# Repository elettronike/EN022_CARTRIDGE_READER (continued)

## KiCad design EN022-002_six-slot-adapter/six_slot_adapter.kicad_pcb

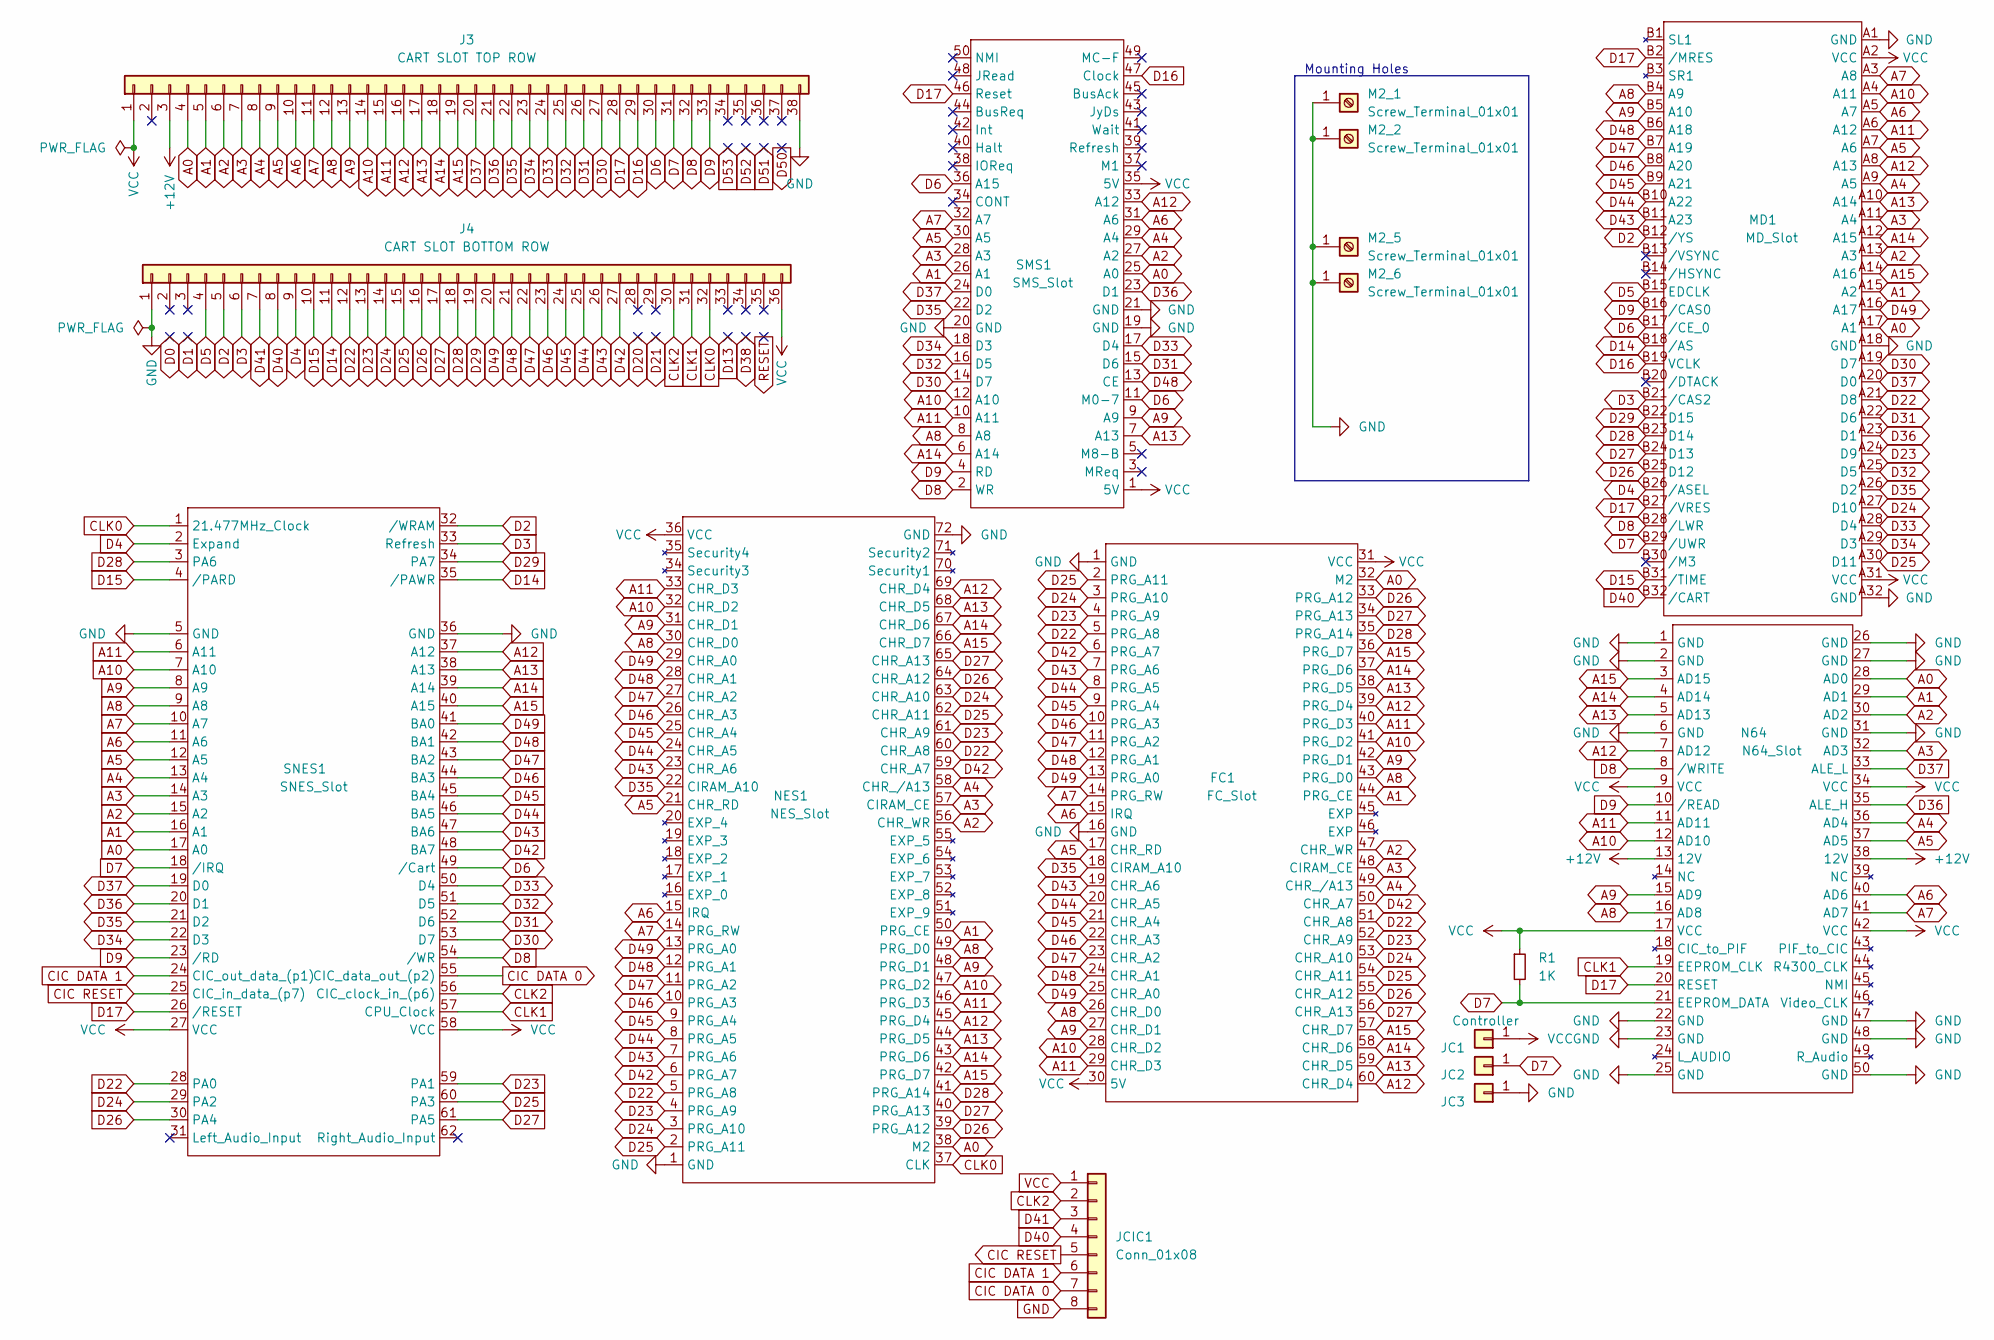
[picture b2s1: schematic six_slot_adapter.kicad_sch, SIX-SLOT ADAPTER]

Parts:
FC1: FC_Slot
J3: CART SLOT TOP ROW; PinSocket_1x38_P2.54mm_Vertical
J4: CART SLOT BOTTOM ROW; PinSocket_1x36_P2.54mm_Vertical
JC1: Controller; PinHeader_1x01_P2.54mm_Vertical
JC2, JC3: Conn_01x01; PinHeader_1x01_P2.54mm_Vertical
JCIC1: Conn_01x08; PinHeader_1x08_P2.54mm_Vertical
M2_1, M2_2, M2_5, M2_6: Screw_Terminal_01x01; MountingHole_2.2mm_M2_ISO7380_Pad
MD1: MD_Slot
N64: N64_Slot; N64 Slot
NES1: NES_Slot
R1: 1K; R_Axial_DIN0207_L6.3mm_D2.5mm_P10.16mm_Horizontal
SMS1: SMS_Slot
SNES1: SNES_Slot; SNES Slot

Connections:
+12V: J3.3, N64.13 (12V), N64.38 (12V)
A0: FC1.32 (M2), J3.4, MD1.A17 (A1), N64.28 (AD0), NES1.38 (M2), SMS1.25 (A0), SNES1.17 (A0)
A1: FC1.44 (PRG_CE), J3.5, MD1.A15 (A2), N64.29 (AD1), NES1.50 (PRG_CE), SMS1.26 (A1), SNES1.16 (A1)
A2: FC1.47 (CHR_WR), J3.6, MD1.A13 (A3), N64.30 (AD2), NES1.56 (CHR_WR), SMS1.27 (A2), SNES1.15 (A2)
A3: FC1.48 (CIRAM_CE), J3.7, MD1.A11 (A4), N64.32 (AD3), NES1.57 (CIRAM_CE), SMS1.28 (A3), SNES1.14 (A3)
A4: FC1.49 (CHR_/A13), J3.8, MD1.A9 (A5), N64.36 (AD4), NES1.58 (CHR_/A13), SMS1.29 (A4), SNES1.13 (A4)
A5: FC1.17 (CHR_RD), J3.9, MD1.A7 (A6), N64.37 (AD5), NES1.21 (CHR_RD), SMS1.30 (A5), SNES1.12 (A5)
A6: FC1.15 (IRQ), J3.10, MD1.A5 (A7), N64.40 (AD6), NES1.15 (IRQ), SMS1.31 (A6), SNES1.11 (A6)
A7: FC1.14 (PRG_RW), J3.11, MD1.A3 (A8), N64.41 (AD7), NES1.14 (PRG_RW), SMS1.32 (A7), SNES1.10 (A7)
A8: FC1.26 (CHR_D0), FC1.43 (PRG_D0), J3.12, MD1.B4 (A9), N64.16 (AD8), NES1.30 (CHR_D0), NES1.49 (PRG_D0), SMS1.8 (A8), SNES1.9 (A8)
A9: FC1.27 (CHR_D1), FC1.42 (PRG_D1), J3.13, MD1.B5 (A10), N64.15 (AD9), NES1.31 (CHR_D1), NES1.48 (PRG_D1), SMS1.9 (A9), SNES1.8 (A9)
A10: FC1.28 (CHR_D2), FC1.41 (PRG_D2), J3.14, MD1.A4 (A11), N64.12 (AD10), NES1.32 (CHR_D2), NES1.47 (PRG_D2), SMS1.12 (A10), SNES1.7 (A10)
A11: FC1.29 (CHR_D3), FC1.40 (PRG_D3), J3.15, MD1.A6 (A12), N64.11 (AD11), NES1.33 (CHR_D3), NES1.46 (PRG_D3), SMS1.10 (A11), SNES1.6 (A11)
A12: FC1.39 (PRG_D4), FC1.60 (CHR_D4), J3.16, MD1.A8 (A13), N64.7 (AD12), NES1.45 (PRG_D4), NES1.69 (CHR_D4), SMS1.33 (A12), SNES1.37 (A12)
A13: FC1.38 (PRG_D5), FC1.59 (CHR_D5), J3.17, MD1.A10 (A14), N64.5 (AD13), NES1.44 (PRG_D5), NES1.68 (CHR_D5), SMS1.7 (A13), SNES1.38 (A13)
A14: FC1.37 (PRG_D6), FC1.58 (CHR_D6), J3.18, MD1.A12 (A15), N64.4 (AD14), NES1.43 (PRG_D6), NES1.67 (CHR_D6), SMS1.6 (A14), SNES1.39 (A14)
A15: FC1.36 (PRG_D7), FC1.57 (CHR_D7), J3.19, MD1.A14 (A16), N64.3 (AD15), NES1.42 (PRG_D7), NES1.66 (CHR_D7), SNES1.40 (A15)
CIC DATA 0: JCIC1.7, SNES1.55 (CIC_data_out_(p2))
CIC DATA 1: JCIC1.6, SNES1.24 (CIC_out_data_(p1))
CIC RESET: JCIC1.5, SNES1.25 (CIC_in_data_(p7))
CLK0: J4.32, NES1.37 (CLK), SNES1.1 (21.477MHz_Clock)
CLK1: J4.31, N64.19 (EEPROM_CLK), SNES1.57 (CPU_Clock)
CLK2: J4.30, JCIC1.2, SNES1.56 (CIC_clock_in_(p6))
D2: J4.5, MD1.B12 (/YS), SNES1.32 (/WRAM)
D3: J4.6, MD1.B21 (/CAS2), SNES1.33 (Refresh)
D4: J4.9, MD1.B26 (/ASEL), SNES1.2 (Expand)
D5: J4.4, MD1.B15 (EDCLK)
D6: J3.30, MD1.B17 (/CE_0), SMS1.11 (M0-7), SMS1.36 (A15), SNES1.49 (/Cart)
D7: J3.31, JC2.1, MD1.B29 (/UWR), N64.21 (EEPROM_DATA), R1.2, SNES1.18 (/IRQ)
D8: J3.32, MD1.B28 (/LWR), N64.8 (/WRITE), SMS1.2 (WR), SNES1.54 (/WR)
D9: J3.33, MD1.B16 (/CAS0), N64.10 (/READ), SMS1.4 (RD), SNES1.23 (/RD)
D14: J4.11, MD1.B18 (/AS), SNES1.35 (/PAWR)
D15: J4.10, MD1.B31 (/TIME), SNES1.4 (/PARD)
D16: J3.29, MD1.B19 (VCLK), SMS1.47 (Clock)
D17: J3.28, MD1.B2 (/MRES), MD1.B27 (/VRES), N64.20 (RESET), SMS1.46 (Reset), SNES1.26 (/RESET)
D22: FC1.5 (PRG_A8), FC1.51 (CHR_A8), J4.12, MD1.A21 (D8), NES1.5 (PRG_A8), NES1.60 (CHR_A8), SNES1.28 (PA0)
D23: FC1.4 (PRG_A9), FC1.52 (CHR_A9), J4.13, MD1.A24 (D9), NES1.4 (PRG_A9), NES1.61 (CHR_A9), SNES1.59 (PA1)
D24: FC1.3 (PRG_A10), FC1.53 (CHR_A10), J4.14, MD1.A27 (D10), NES1.3 (PRG_A10), NES1.63 (CHR_A10), SNES1.29 (PA2)
D25: FC1.2 (PRG_A11), FC1.54 (CHR_A11), J4.15, MD1.A30 (D11), NES1.2 (PRG_A11), NES1.62 (CHR_A11), SNES1.60 (PA3)
D26: FC1.33 (PRG_A12), FC1.55 (CHR_A12), J4.16, MD1.B25 (D12), NES1.39 (PRG_A12), NES1.64 (CHR_A12), SNES1.30 (PA4)
D27: FC1.34 (PRG_A13), FC1.56 (CHR_A13), J4.17, MD1.B24 (D13), NES1.40 (PRG_A13), NES1.65 (CHR_A13), SNES1.61 (PA5)
D28: FC1.35 (PRG_A14), J4.18, MD1.B23 (D14), NES1.41 (PRG_A14), SNES1.3 (PA6)
D29: J4.19, MD1.B22 (D15), SNES1.34 (PA7)
D30: J3.27, MD1.A19 (D7), SMS1.14 (D7), SNES1.53 (D7)
D31: J3.26, MD1.A22 (D6), SMS1.15 (D6), SNES1.52 (D6)
D32: J3.25, MD1.A25 (D5), SMS1.16 (D5), SNES1.51 (D5)
D33: J3.24, MD1.A28 (D4), SMS1.17 (D4), SNES1.50 (D4)
D34: J3.23, MD1.A29 (D3), SMS1.18 (D3), SNES1.22 (D3)
D35: FC1.18 (CIRAM_A10), J3.22, MD1.A26 (D2), NES1.22 (CIRAM_A10), SMS1.22 (D2), SNES1.21 (D2)
D36: J3.21, MD1.A23 (D1), N64.35 (ALE_H), SMS1.23 (D1), SNES1.20 (D1)
D37: J3.20, MD1.A20 (D0), N64.33 (ALE_L), SMS1.24 (D0), SNES1.19 (D0)
D40: J4.8, JCIC1.4, MD1.B32 (/CART)
D41: J4.7, JCIC1.3
D42: FC1.6 (PRG_A7), FC1.50 (CHR_A7), J4.27, NES1.6 (PRG_A7), NES1.59 (CHR_A7), SNES1.48 (BA7)
D43: FC1.7 (PRG_A6), FC1.19 (CHR_A6), J4.26, MD1.B11 (A23), NES1.7 (PRG_A6), NES1.23 (CHR_A6), SNES1.47 (BA6)
D44: FC1.8 (PRG_A5), FC1.20 (CHR_A5), J4.25, MD1.B10 (A22), NES1.8 (PRG_A5), NES1.24 (CHR_A5), SNES1.46 (BA5)
D45: FC1.9 (PRG_A4), FC1.21 (CHR_A4), J4.24, MD1.B9 (A21), NES1.9 (PRG_A4), NES1.25 (CHR_A4), SNES1.45 (BA4)
D46: FC1.10 (PRG_A3), FC1.22 (CHR_A3), J4.23, MD1.B8 (A20), NES1.10 (PRG_A3), NES1.26 (CHR_A3), SNES1.44 (BA3)
D47: FC1.11 (PRG_A2), FC1.23 (CHR_A2), J4.22, MD1.B7 (A19), NES1.11 (PRG_A2), NES1.27 (CHR_A2), SNES1.43 (BA2)
D48: FC1.12 (PRG_A1), FC1.24 (CHR_A1), J4.21, MD1.B6 (A18), NES1.12 (PRG_A1), NES1.28 (CHR_A1), SMS1.13 (CE), SNES1.42 (BA1)
D49: FC1.13 (PRG_A0), FC1.25 (CHR_A0), J4.20, MD1.A16 (A17), NES1.13 (PRG_A0), NES1.29 (CHR_A0), SNES1.41 (BA0)
GND: FC1.1 (GND), FC1.16 (GND), J3.38, J4.1, JC3.1, JCIC1.8, M2_1.1, M2_2.1, M2_5.1, M2_6.1, MD1.A1 (GND), MD1.A18 (GND), MD1.A32 (GND), N64.1 (GND), N64.2 (GND), N64.6 (GND), N64.22 (GND), N64.23 (GND), N64.25 (GND), N64.26 (GND), N64.27 (GND), N64.31 (GND), N64.47 (GND), N64.48 (GND), N64.50 (GND), NES1.1 (GND), NES1.72 (GND), SMS1.19 (GND), SMS1.20 (GND), SMS1.21 (GND), SNES1.5 (GND), SNES1.36 (GND)
VCC: FC1.30 (5V), FC1.31 (VCC), J3.1, J4.36, JC1.1, JCIC1.1, MD1.A2 (VCC), MD1.A31 (VCC), N64.9 (VCC), N64.17 (VCC), N64.34 (VCC), N64.42 (VCC), NES1.36 (VCC), R1.1, SMS1.1 (5V), SMS1.35 (5V), SNES1.27 (VCC), SNES1.58 (VCC)

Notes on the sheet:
Mounting Holes

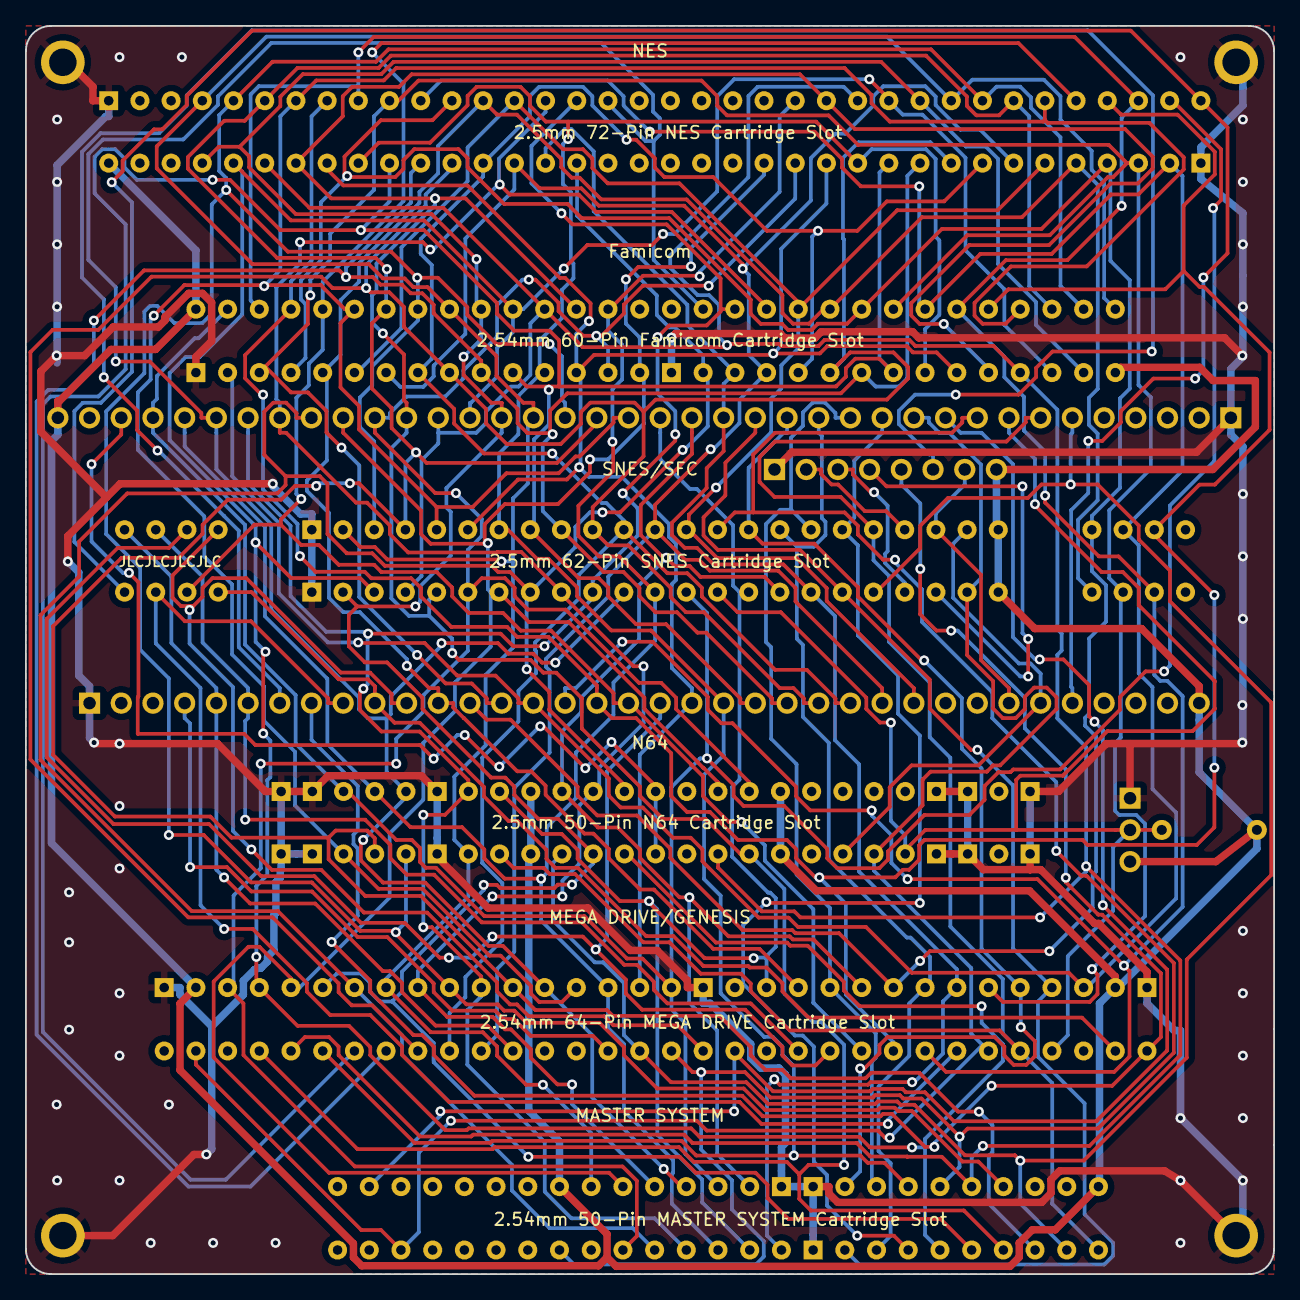
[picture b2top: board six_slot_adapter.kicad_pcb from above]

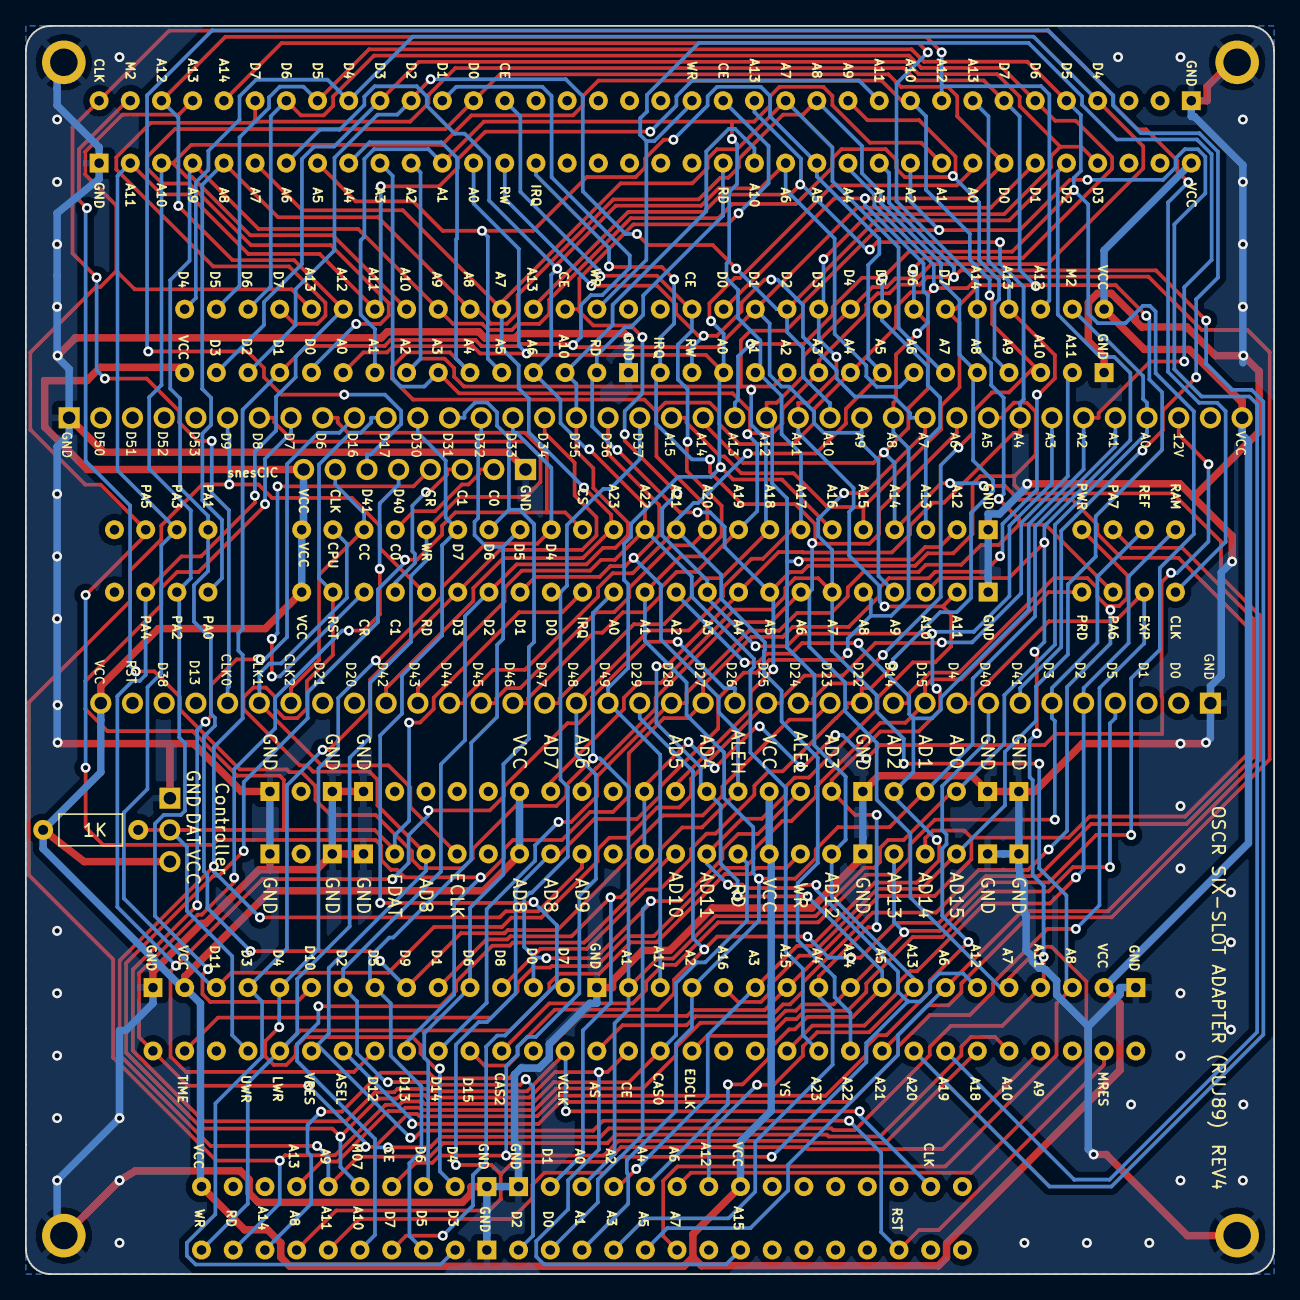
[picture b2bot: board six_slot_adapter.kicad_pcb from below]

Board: 2 copper layers, 100.0 x 100.0 mm, 17 parts (6 on the bottom side), 63 nets.

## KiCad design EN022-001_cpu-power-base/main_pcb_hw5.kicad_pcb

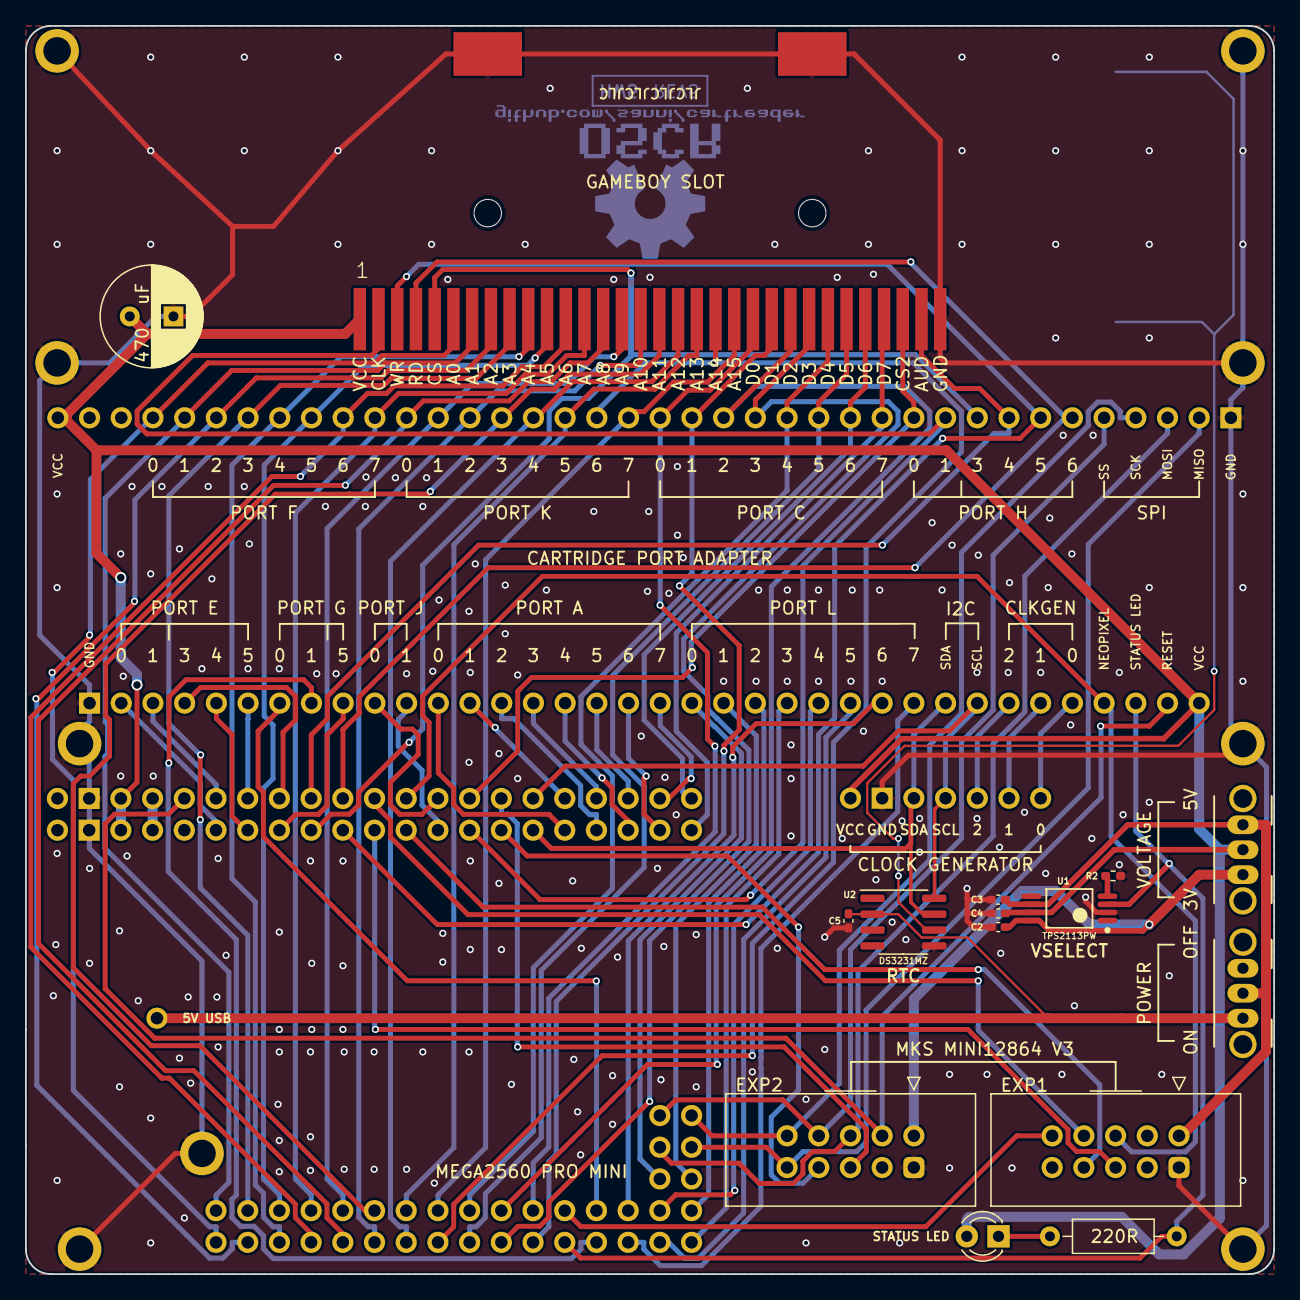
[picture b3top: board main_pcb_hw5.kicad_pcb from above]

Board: 2 copper layers, 100.0 x 100.0 mm, 30 parts (1 on the bottom side), 83 nets.

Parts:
BT1: CR1616
C1: 470u; CP_Radial_D8.0mm_P3.50mm
C2, C3, C5: 0.1u; C_0402_1005Metric_Pad0.74x0.62mm_HandSolder
C4: 10u; C_0402_1005Metric_Pad0.74x0.62mm_HandSolder
D1: LED; LED_D3.0mm
J1: MEGA BOTTOM; MEGA2560_PRO_MINI
J3: CART SLOT TOP ROW; Cartridge_Port_Adapter-Back
J4: CART SLOT FRONT ROW; Cartridge_Port_Adapter-Front
J6: 5V USB; PinHeader_1x01_P2.54mm_Vertical
J7: Conn_01x07; Clock_Generator_Header
J8: EXP2; LCD_Header
J9: EXP1; LCD_Header
J10: GBA_Slot; GBA-SLOT-B
M2_1, M2_2, M2_3, M2_4, M2_5, M2_6, M2_7, M2_8, M2_9: Screw_Terminal_01x01; MountingHole_2.2mm_M2_ISO7380_Pad
R1: 220R; R_Axial_DIN0207_L6.3mm_D2.5mm_P10.16mm_Horizontal
R2: 560R; R_0402_1005Metric_Pad0.72x0.64mm_HandSolder
SW1: VOLTAGE; Power_Switch
SW2: POWER; Power_Switch
U1: TPS2113PW; Texas_Instruments-TPS2113PW-Level_A
U2: DS3231MZ; SOIC-8_3.9x4.9mm_P1.27mm

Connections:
+3.3VA: J1.35 (3V3), J1.36 (3V3)
+3V3: C2.2, J8.1, SW1.1 (A), U1.8 (IN1)
+5V: C3.1, J9.1, SW1.3 (C), SW2.2 (B), U1.6 (IN2)
+BATT: BT1.1 (+), U2.6 (VBAT)
A0: J1.73 (A0), J3.4, J10.6 (AD0)
A1: J1.74 (A1), J3.5, J10.7 (AD1)
A2: J1.71 (A2), J3.6, J10.8 (AD2)
A3: J1.72 (A3), J3.7, J10.9 (AD3)
A4: J1.69 (A4), J3.8, J10.10 (AD4)
A5: J1.70 (A5), J3.9, J10.11 (AD5)
A6: J1.67 (A6), J3.10, J10.12 (AD6)
A7: J1.68 (A7), J3.11, J10.13 (AD7)
A8: J1.65 (A8), J3.12, J10.14 (AD8)
A9: J1.66 (A9), J3.13, J10.15 (AD9)
A10: J1.63 (A10), J3.14, J10.16 (AD10)
A11: J1.64 (A11), J3.15, J10.17 (AD11)
A12: J1.61 (A12), J3.16, J10.18 (AD12)
A13: J1.62 (A13), J3.17, J10.19 (AD13)
A14: J1.59 (A14), J3.18, J10.20 (AD14)
A15: J1.60 (A15), J3.19, J10.21 (AD15)
CLK0: J4.32, J7.7
CLK1: J4.31, J7.6
CLK2: J4.30, J7.5
D0: J1.31 (D0), J4.2
D1: J1.32 (D1), J4.3
D2: J1.29 (D2), J4.5
D3: J1.30 (D3), J4.6
D4: J1.27 (D4), J4.9
D5: J1.28 (D5), J4.4
D6: J1.25 (D6), J3.30, J10.5 (CS1)
D7: J1.26 (D7), J3.31, J10.31 (AUD_IRQ)
D8: J1.23 (D8), J3.32, J10.3 (WR)
D9: J1.24 (D9), J3.33, J10.4 (RD)
D10: J1.21 (D10), J9.6
D11: J1.22 (D11), J9.7
D12: J1.19 (D12), J9.8
D13: J1.20 (D13), J4.33, J9.5
D14: J1.17 (D14), J4.11
D15: J1.18 (D15), J4.10
D16: J1.15 (D16), J3.29, J10.2 (CLK)
D17: J1.16 (D17), J3.28, J10.30 (RST_CS2)
D18: J1.13 (D18), J8.8
D19: J1.14 (D19), J8.6
D20: J1.11 (D20), J4.28, J7.3, U2.7 (SDA)
D21: J1.12 (D21), J4.29, J7.4, U2.8 (SCL)
D22: J1.9 (D22), J4.12
D23: J1.10 (D23), J4.13
D24: J1.7 (D24), J4.14
D25: J1.8 (D25), J4.15
D26: J1.5 (D26), J4.16
D27: J1.6 (D27), J4.17
D28: J1.3 (D28), J4.18
D29: J1.4 (D29), J4.19
D30: J1.1 (D30), J3.27, J10.29 (D7_A23)
D31: J1.2 (D31), J3.26, J10.28 (D6_A22)
D32: J1.57 (D32), J3.25, J10.27 (D5_A21)
D33: J1.58 (D33), J3.24, J10.26 (D4_A20)
D34: J1.55 (D34), J3.23, J10.25 (D3_A19)
D35: J1.56 (D35), J3.22, J10.24 (D2_A18)
D36: J1.53 (D36), J3.21, J10.23 (D1_A17)
D37: J1.54 (D37), J3.20, J10.22 (D0_A16)
D38: J1.51 (D38), J4.34, R1.2, U1.3 (VSNS)
D39: J1.52 (D39), J9.9
D40: J1.49 (D40), J4.8
D41: J1.50 (D41), J4.7
D42: J1.47 (D42), J4.27
D43: J1.48 (D43), J4.26
D44: J1.45 (D44), J4.25
D45: J1.46 (D45), J4.24
D46: J1.43 (D46), J4.23
D47: J1.44 (D47), J4.22
D48: J1.76 (D48), J4.21
D49: J1.75 (D49), J4.20
D50: J1.78 (D50), J3.37, J8.10
D51: J1.77 (D51), J3.36, J8.5
D52: J1.80 (D52), J3.35, J8.9
D53: J1.79 (D53), J3.34, J8.7
GND: BT1.2 (-), C1.2, C2.1, C3.2, C4.2, C5.2, J1.39 (GND), J1.40 (GND), J3.38, J4.1, J7.2, J8.2, J9.2, J10.32 (GND), J10.33, J10.34, M2_1.1, M2_2.1, M2_3.1, M2_4.1, M2_5.1, M2_6.1, M2_7.1, M2_8.1, M2_9.1, R2.1, U1.2 (~EN), U1.5 (GND), U2.5 (GND)
unnamed: D1.1 (K), R1.1
unnamed: R2.2, U1.4 (ILIM)
RESET: J1.34 (RST), J4.35, J8.3
VBUS: C5.1, J6.1, SW2.1 (A), U2.2 (VCC)
VCC: C1.1, C4.1, D1.2 (A), J1.37 (5V), J1.38 (5V), J3.1, J4.36, J7.1, J10.1 (VCC), SW1.2 (B), U1.7 (OUT)

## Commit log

2024-09-13 Removed underscore of README.md
2024-09-19 OSCR symbol library
2024-09-19 OSCR footprints
2024-09-19 CPU board project
2024-09-19 slot adapter project
2024-09-19 project rename
2024-09-19 applied page layout
2024-09-19 check holeposition
2024-09-19 mountin holes position
2024-09-19 Removed atmega board connector
2024-09-19 update GBA slot ground pin name to SH1/2
2024-09-19 added 3D model to GBA slot connector
2024-09-19 updateted GBA slot
2024-09-19 pcb traces cleanup
2024-09-22 modified CH32V307 symbol
2024-09-22 added license
2024-09-22 GBA slot technical ref
2024-09-22 cpu pinout and bus references
2026-01-24 added power section
2026-01-25 first cimplete version of CPU POWER BASE
2026-01-25 moved GBA connector step file to footprint folder
